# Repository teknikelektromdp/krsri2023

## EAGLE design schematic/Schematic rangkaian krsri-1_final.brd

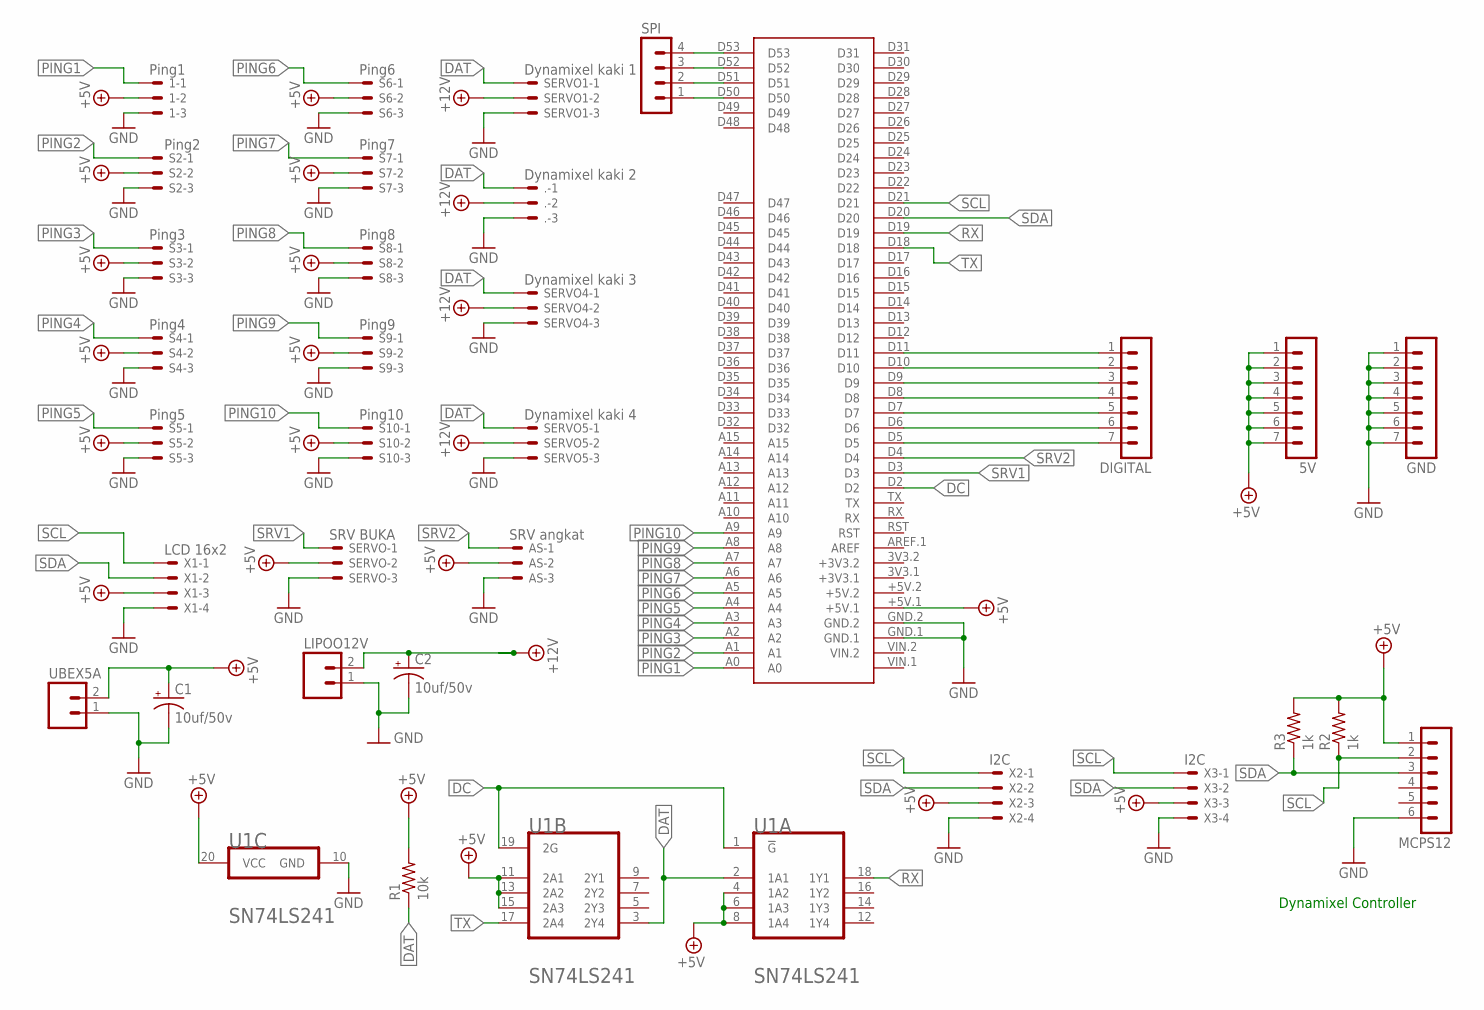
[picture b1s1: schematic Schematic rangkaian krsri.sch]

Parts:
1: Ping1; 22-23-2031
5V: MA07-1
.: Dynamixel kaki 2; 22-23-2031
AS: SRV angkat; 22-23-2031
C1, C2: 10uf/50v; E5-8,5
DIGITAL: MA07-1
GND: MA07-1
LIPOO12V: M02; 02P
MCPS12: MA06-1
R1: 10k; 0204/7
R2, R3: 1k; 0204/7
S2: Ping2; 22-23-2031
S3: Ping3; 22-23-2031
S4: Ping4; 22-23-2031
S5: Ping5; 22-23-2031
S6: Ping6; 22-23-2031
S7: Ping7; 22-23-2031
S8: Ping8; 22-23-2031
S9: Ping9; 22-23-2031
S10: Ping10; 22-23-2031
SERVO: SRV BUKA; 22-23-2031
SERVO1: Dynamixel kaki 1; 22-23-2031
SERVO4: Dynamixel kaki 3; 22-23-2031
SERVO5: Dynamixel kaki 4; 22-23-2031
SPI: MA04-1
U1: TEXAS_INSTRUMENTS_SN74LS241TEXAS_INSTRUMENTS_SN74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; TEXAS_INSTRUMENTS_SN74LS241_0
U$1: MEGA2560_MIKRO
UBEX5A: M02; 02P
X1: LCD 16x2; 22-23-2041
X2, X3: I2C; 22-23-2041

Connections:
+5V: 1.2, 5V.1, 5V.2, 5V.3, 5V.4, 5V.5, 5V.6, 5V.7, AS.2, C1.+, MCPS12.1, R1.2, R2.2, R3.2, S2.2, S3.2, S4.2, S5.2, S6.2, S7.2, S8.2, S9.2, S10.2, SERVO.2, U1.4 (1A2), U1.6 (1A3), U1.8 (1A4), U1.11 (2A1), U1.13 (2A2), U1.15 (2A3), U1.20 (VCC), U$1.+5V.1, UBEX5A.2, X1.3, X2.3, X3.3
+12V: ..2, C2.+, LIPOO12V.2, SERVO1.2, SERVO4.2, SERVO5.2
DAT: ..1, R1.1, SERVO1.1, SERVO4.1, SERVO5.1, U1.2 (1A1), U1.3 (2Y4)
DC: U1.1 (!G!), U1.19 (2G), U$1.D2
GND: 1.3, ..3, AS.3, C1.-, C2.-, GND.1, GND.2, GND.3, GND.4, GND.5, GND.6, GND.7, LIPOO12V.1, MCPS12.6, S2.3, S3.3, S4.3, S5.3, S6.3, S7.3, S8.3, S9.3, S10.3, SERVO.3, SERVO1.3, SERVO4.3, SERVO5.3, U1.10 (GND), U$1.GND.1, U$1.GND.2, UBEX5A.1, X1.4, X2.4, X3.4
unnamed: SPI.4, U$1.D53
unnamed: DIGITAL.7, U$1.D5
unnamed: DIGITAL.6, U$1.D6
unnamed: DIGITAL.5, U$1.D7
unnamed: DIGITAL.4, U$1.D8
unnamed: DIGITAL.3, U$1.D9
unnamed: DIGITAL.2, U$1.D10
unnamed: DIGITAL.1, U$1.D11
unnamed: SPI.3, U$1.D52
unnamed: SPI.2, U$1.D51
unnamed: SPI.1, U$1.D50
PING1: 1.1, U$1.A0
PING2: S2.1, U$1.A1
PING3: S3.1, U$1.A2
PING4: S4.1, U$1.A3
PING5: S5.1, U$1.A4
PING6: S6.1, U$1.A5
PING7: S7.1, U$1.A6
PING8: S8.1, U$1.A7
PING9: S9.1, U$1.A8
PING10: S10.1, U$1.A9
RX: U1.18 (1Y1), U$1.D19
SCL: MCPS12.2, R2.1, U$1.D21, X1.1, X2.1, X3.1
SDA: MCPS12.3, R3.1, U$1.D20, X1.2, X2.2, X3.2
SRV1: SERVO.1, U$1.D3
SRV2: AS.1, U$1.D4
TX: U1.17 (2A4), U$1.D18

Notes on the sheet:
Dynamixel Controller

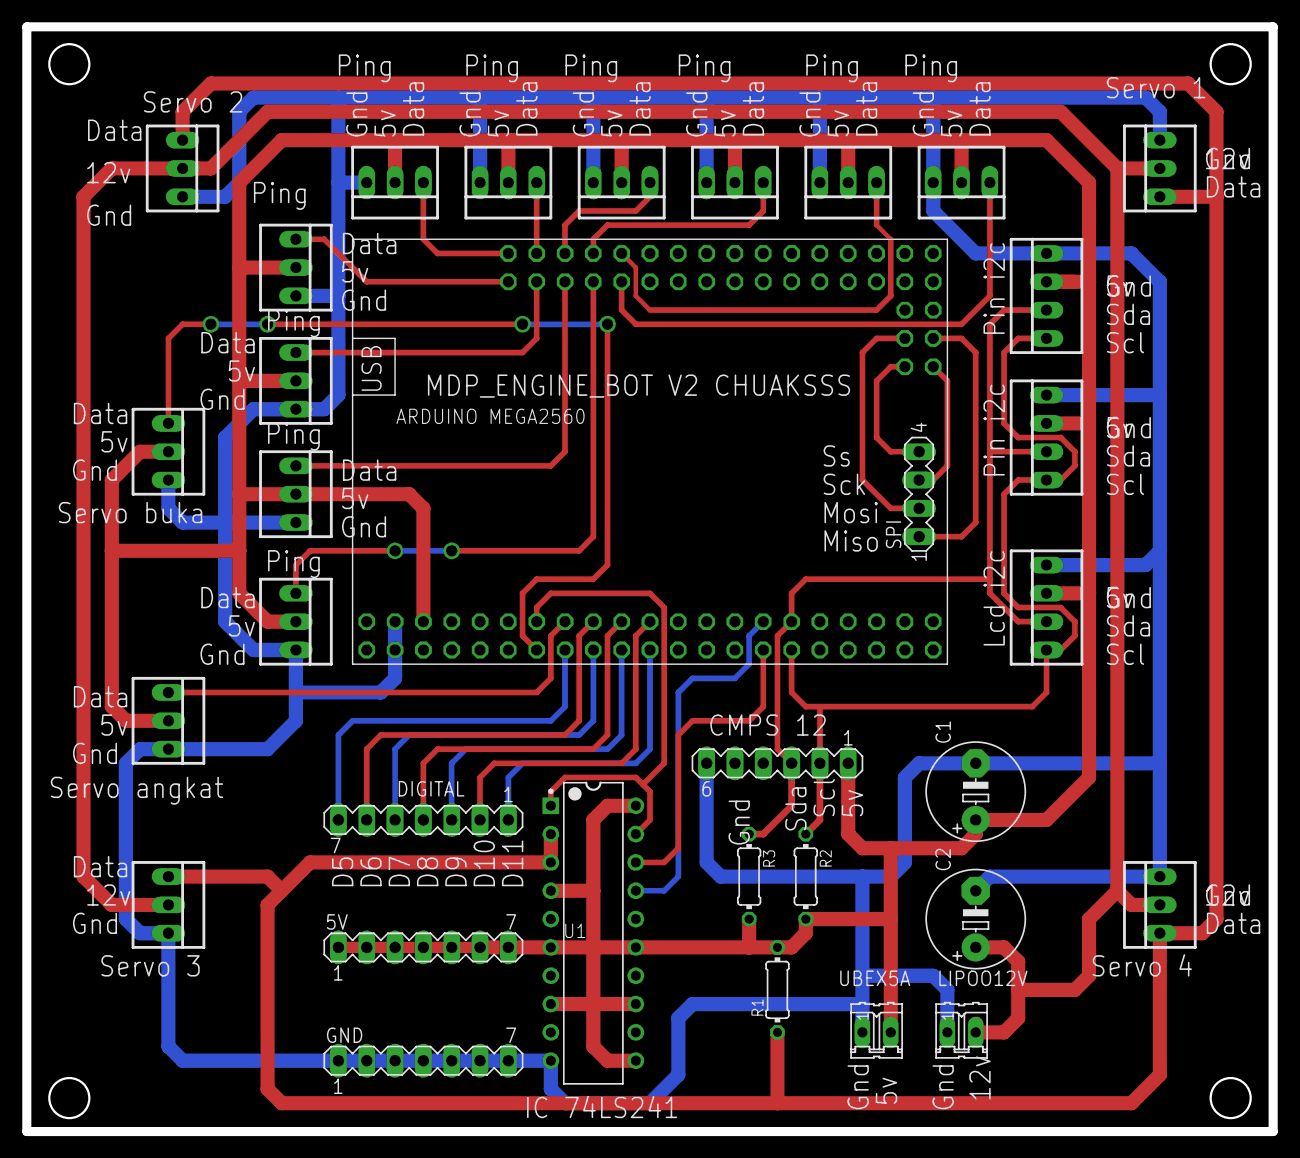
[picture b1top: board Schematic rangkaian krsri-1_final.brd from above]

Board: 2 copper layers, 111.8 x 99.1 mm, 33 parts (0 on the bottom side), 32 nets.

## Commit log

2023-03-27 add schematic and pcb
2023-03-27 add PAT
2023-04-05 Dynmixel and translated Inverse Kinematics
2023-04-05 Coxa Femur Tibia cmall change
2023-04-05 Adjusting leg limit
2023-04-06 Adjustment for Algorithm
2023-04-08 Added Bluetooth Module test and Reset
2023-04-09 add inverse_kinematics and servo_calibration programs
2023-04-11 Adding some of last year program
2023-04-11 Additional function for Dynamixel Movement with inverse kinematics calculations
2023-04-12 Added Robot's Legs Movement
2023-04-13 Finally done with Tripod Gait
2023-04-14 added trot movement
2023-04-16 Rename dynamixel_inverse.ino to inverse_with_trajectory.ino
2023-04-17 after adding more length on femur
2023-04-18 17.03 18/04/2023
2023-04-25 Add Gait Algorithms
2023-04-27 27/04/2023 18:19
2023-04-29 29/04/2023 17:46
2023-05-02 02/05/2023 19.20
2023-05-02 19.22
2023-05-02 Add Log Data
2023-05-02 Add RF24 Library
2023-05-03 03/05/2023 19.13
2023-05-05 05/05/2023 19.28 capable of doing obstacles until the marble obstacle individually
2023-05-08 19.14 08/05/2023
2023-05-09 19.09 09/05/2023
2023-05-10 19.20 10/05/2023
2023-05-11 20.09 11/05/2023
2023-05-15 19.23 15/05/2023
2023-05-16 18 56 16/05/2023 second algorithm for putting victim
2023-05-17 17/05/2023 18:34 currently the best possible algorithm (after the arena and robot are checked by judges
2023-05-19 19/05/2023 18:51
2023-05-20 20/05/2023 10:36
2023-05-20 Add Gripper with IK algorithm
2023-05-20 20/05/2023 13:46
2023-05-22 22/05/2023 19:18
2023-05-23 23/05/2023 19.58 capable of saving 2 victim consecutively
2023-05-24 24/05/2023 19.28
2023-05-25 25/05/2023 15.04
2023-05-25 25/05/2023 19.38
2023-05-26 26/05/2023 19.28
2023-05-27 27/05/2023 20.25
2023-05-28 28/05/2023 19.52
2023-05-29 29/05/2023 17.46
2023-05-29 30/05/2023 5.36
2023-05-30 30/05/2023 9.01
2023-05-30 30/05/2023 12.18
2023-05-30 30/05/2023 18.01
2023-05-30 30/05/2023 22.52
2023-05-31 31/05/2023 17.37
2023-07-20 add frame
